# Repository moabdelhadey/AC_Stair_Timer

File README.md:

# AC Stair Timer (High-Load AC Triggered Timer Circuit using NE555)

An affordable and energy-efficient timer circuit designed to control stairway lighting. The circuit is triggered by an AC signal from any stair switch and automatically turns off the light after a user-defined delay. It consumes **no power while idle**, thanks to a latch mechanism that cuts off the entire supply when the relay opens.

---

## ✅ Features

- **AC Triggered**: Can be triggered from any AC switch connected in the stairway.
- **Zero Power Consumption in Standby**: Power supply is wired in series with the load. Once the relay disconnects the load, the entire circuit powers off.
- **Handles up to 10A Load**: Suitable for high-power lighting circuits.
- **Adjustable Timer (0–15 min)**: Controlled by a potentiometer. Can be extended using standard NE555 timing calculations.
- **Low-Cost and Simple Components**: Built around NE555, a relay, and basic resistors/capacitors.
- **Single-Layer PCB**: Easy for home etching or low-cost fabrication.
- **Local Alternative to Imported Units**: Provides the same functionality at a fraction of the cost.

---

## 🧩 Main Components

- NE555 Timer IC
- Relay (10A rated)
- Potentiometer
- Capacitors and resistors

---

## ⏱️ Time Adjustment Formula

You can calculate or extend the timing duration using the standard NE555 monostable formula:

```
T ≈ 1.1 × R × C
```

Where:
- `R` is the potentiometer (resistance in ohms)
- `C` is the timing capacitor (in farads)

---

## 📁 Project Files

- **KiCad** design files (schematic + PCB layout)
- **Proteus** simulation file
- **STEP file** (3D model of assembled circuit)
- **PDFs** for manual PCB etching (Top layer, Drill, Silkscreen)
- Real-life **assembly images**

---

## 🧪 Project Status

- ✅ **Version 1** tested successfully in a real stairway.
- 🛠️ **Version 2** in development with enhancements.

---

## ⚠️ Safety Notes

- Ensure proper isolation when connecting to AC.
- Add relay cooling if switching high loads frequently.

---

## 📜 License

This project is open source.

---

## 📷 Images

---

## 📬 Contact

Mohamed Abdelhady — For inquiries, feel free to reach out if any issue arises.

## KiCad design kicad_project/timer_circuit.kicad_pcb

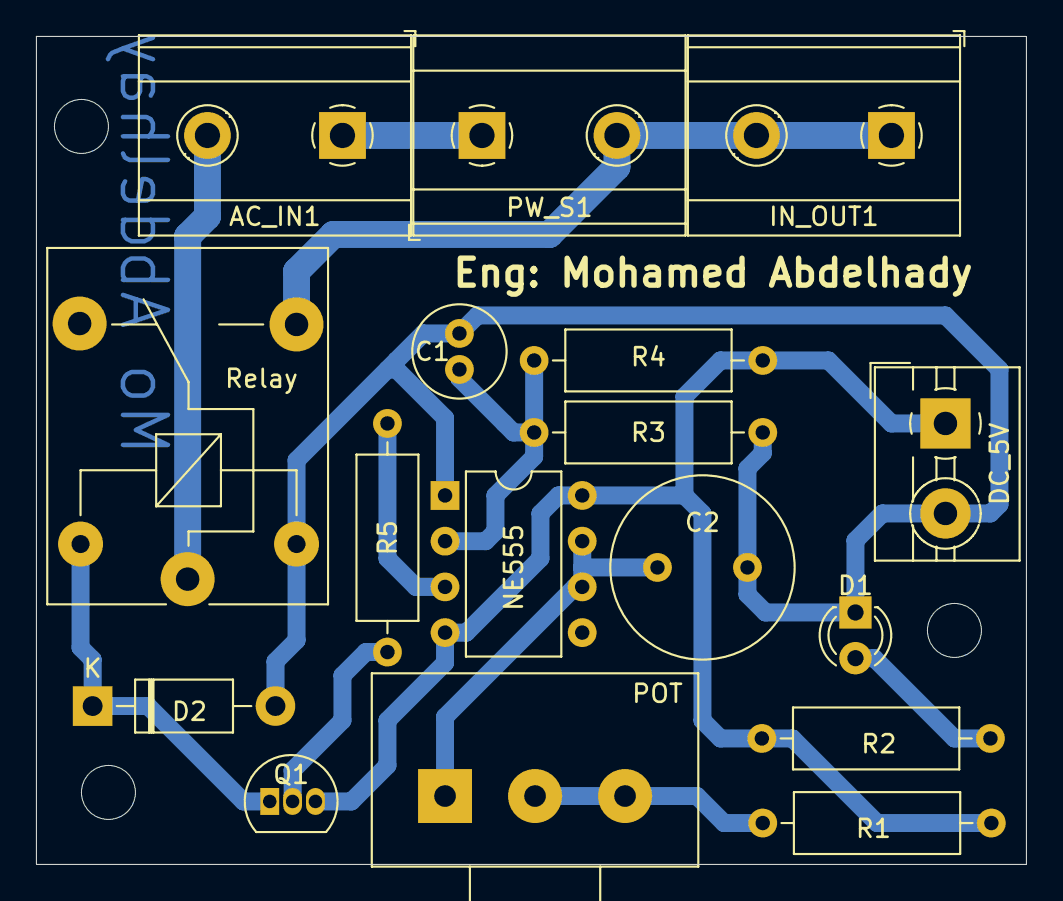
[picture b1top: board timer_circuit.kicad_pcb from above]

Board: 2 copper layers, 55.0 x 46.0 mm, 17 parts (0 on the bottom side), 12 nets.

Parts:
AC_IN1: Screw_Terminal_01x02; TerminalBlock_MetzConnect_Type175_RT02702HBLC_1x02_P7.50mm_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
C1: 1uF; C_Radial_D5.0mm_H11.0mm_P2.00mm
C2: 470uF; C_Radial_D10.0mm_H12.5mm_P5.00mm
D1: LED; LED_D3.0mm
D2: 1N4007; D_DO-41_SOD81_P10.16mm_Horizontal
DC_5V: Screw_Terminal_01x02; TerminalBlock_MaiXu_MX126-5.0-02P_1x02_P5.00mm
IN_OUT1: Screw_Terminal_01x02; TerminalBlock_MetzConnect_Type175_RT02702HBLC_1x02_P7.50mm_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
NE555: NE555P; DIP-8_W7.62mm
POT: R_Potentiometer; Potentiometer_Alps_RK163_Single_Horizontal
PW_S1: Screw_Terminal_01x02; TerminalBlock_MetzConnect_Type175_RT02702HBLC_1x02_P7.50mm_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
Q1: 2N3904; TO-92L_Inline
R1, R3: 100K; R_Axial_DIN0309_L9.0mm_D3.2mm_P12.70mm_Horizontal
R2: 220R; R_Axial_DIN0309_L9.0mm_D3.2mm_P12.70mm_Horizontal
R4: 10K; R_Axial_DIN0309_L9.0mm_D3.2mm_P12.70mm_Horizontal
R5: 500R; R_Axial_DIN0309_L9.0mm_D3.2mm_P12.70mm_Horizontal
Relay: 5V; Relay_SPDT_SANYOU_SRD_Series_Form_C

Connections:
GND: C1.2, C2.2, D1.1 (K), D2.2 (A), DC_5V.2, NE555.1 (GND), R3.1, Relay.2
unnamed: AC_IN1.1, PW_S1.1
unnamed: AC_IN1.2, Relay.1
unnamed: D1.2 (A), R2.1
unnamed: D2.1 (K), Q1.1 (E), Relay.5
unnamed: IN_OUT1.1, IN_OUT1.2, PW_S1.2, Relay.3
unnamed: Q1.2 (B), R5.2
unnamed: POT.2, POT.3, R1.1
unnamed: C2.1, NE555.6 (THR), NE555.7 (DIS), POT.1
unnamed: NE555.3 (Q), R5.1
unnamed: C1.1, NE555.2 (TR), R3.2, R4.2
VCC: DC_5V.1, NE555.4 (R), NE555.8 (VCC), Q1.3 (C), R1.2, R2.2, R4.1

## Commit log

2025-05-30 Create fp-info-cache
